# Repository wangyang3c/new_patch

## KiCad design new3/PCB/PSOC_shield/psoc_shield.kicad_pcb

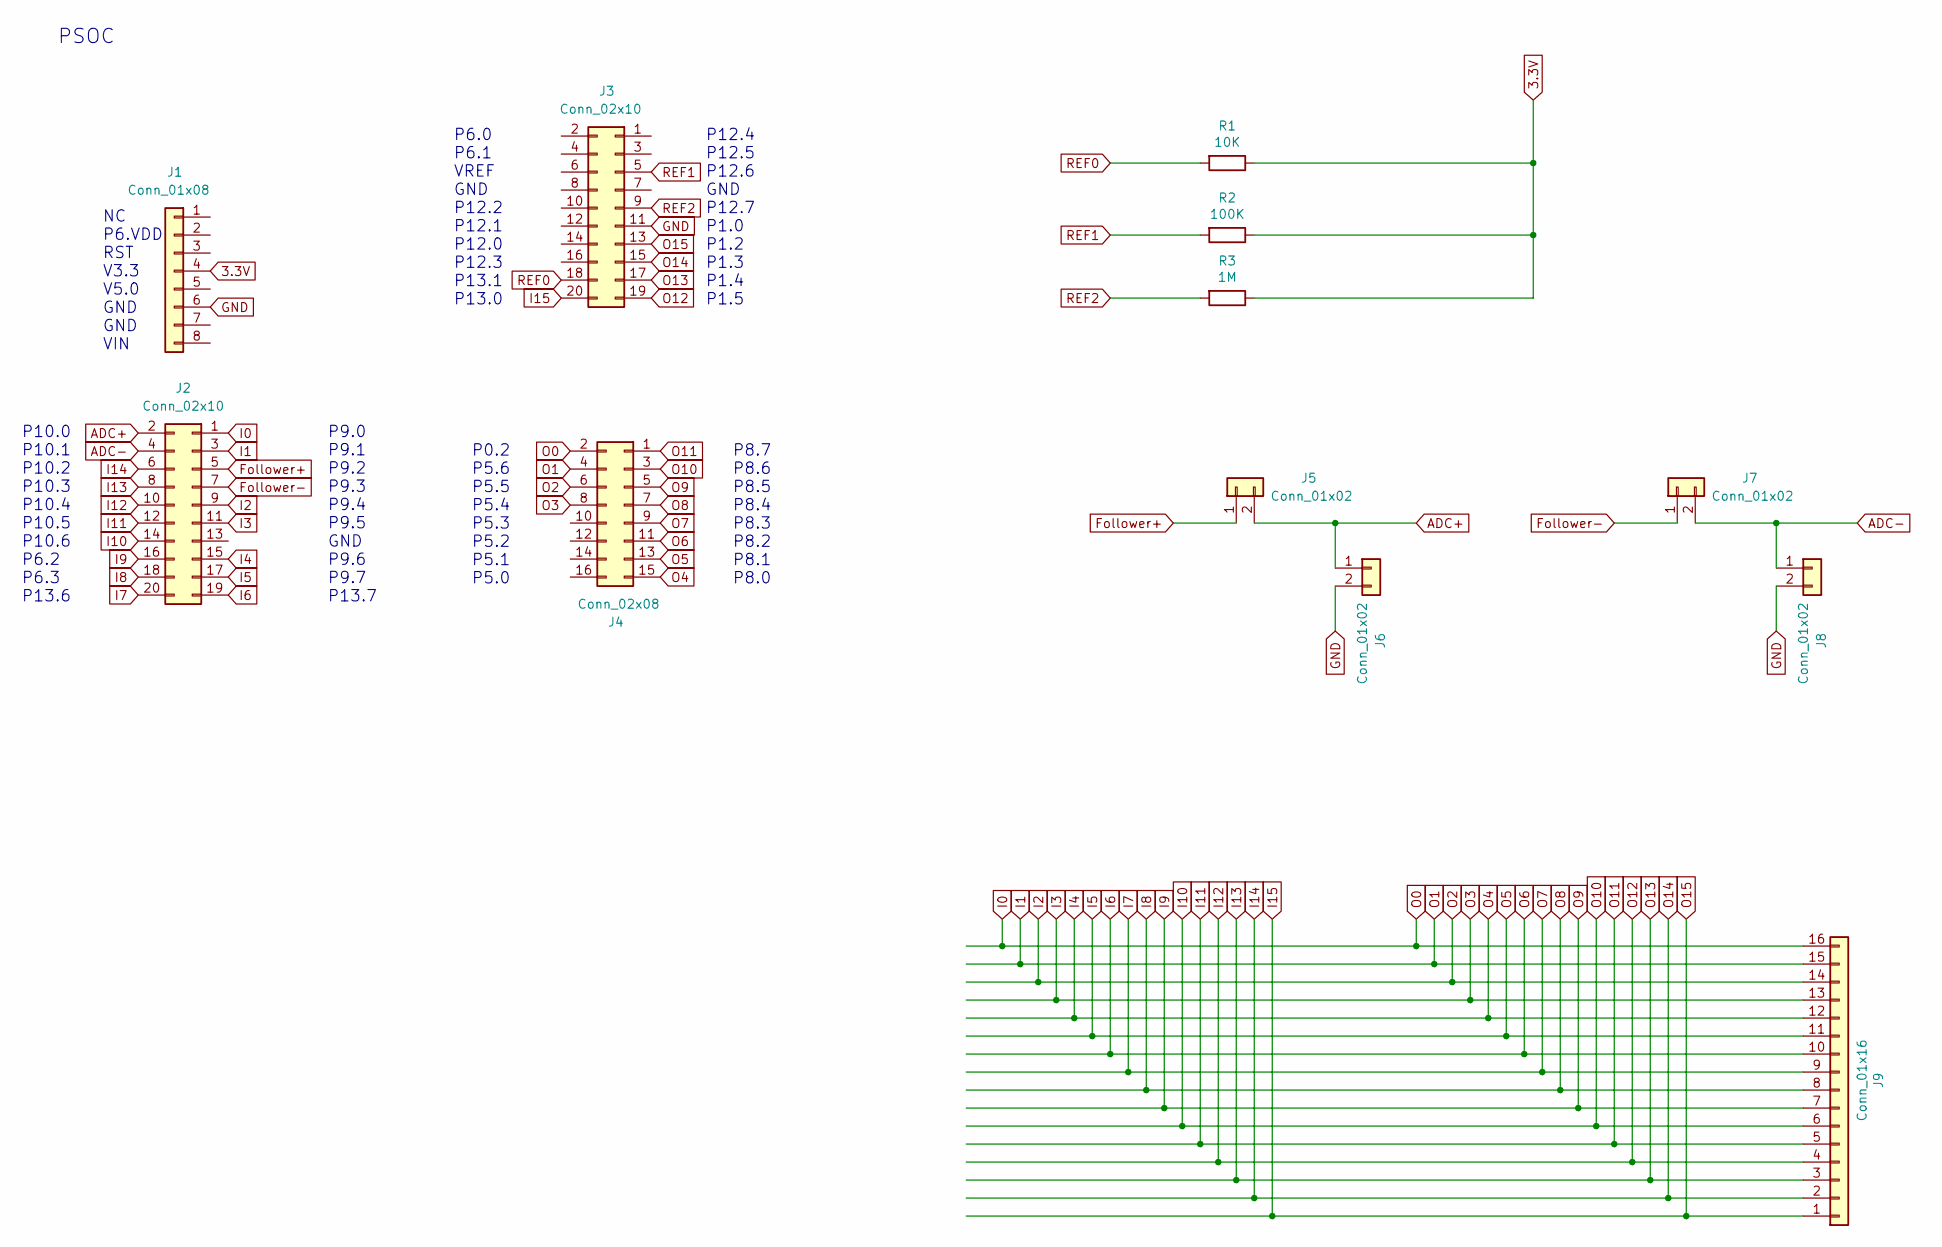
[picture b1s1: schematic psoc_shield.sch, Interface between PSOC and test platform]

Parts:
J1: Conn_01x08; PinSocket_1x08_P2.54mm_Vertical
J2, J3: Conn_02x10; PinSocket_2x10_P2.54mm_Vertical
J4: Conn_02x08; PinSocket_2x08_P2.54mm_Vertical
J5, J6, J7, J8: Conn_01x02; PinSocket_1x02_P2.54mm_Vertical
J9: Conn_01x16; FH19SC16S05SH09
R1: 10K; R_0805_2012Metric
R2: 100K; R_0805_2012Metric
R3: 1M; R_0805_2012Metric

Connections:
3.3V: J1.4, R1.1, R2.1, R3.1
ADC+: J2.2, J5.2, J6.1
ADC-: J2.4, J7.2, J8.1
Follower+: J2.5, J5.1
Follower-: J2.7, J7.1
GND: J1.6, J3.11, J6.2, J8.2
I0: J2.1, J4.2, J9.16
I1: J2.3, J4.4, J9.15
I2: J2.9, J4.6, J9.14
I3: J2.11, J4.8, J9.13
I4: J2.15, J4.15, J9.12
I5: J2.17, J4.13, J9.11
I6: J2.19, J4.11, J9.10
I7: J2.20, J4.9, J9.9
I8: J2.18, J4.7, J9.8
I9: J2.16, J4.5, J9.7
I10: J2.14, J4.3, J9.6
I11: J2.12, J4.1, J9.5
I12: J2.10, J3.19, J9.4
I13: J2.8, J3.17, J9.3
I14: J2.6, J3.15, J9.2
I15: J3.13, J3.20, J9.1
REF0: J3.18, R1.2
REF1: J3.5, R2.2
REF2: J3.9, R3.2

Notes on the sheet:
PSOC
P10.0 P10.1 P10.2 P10.3 P10.4 P10.5 P10.6 P6.2 P6.3 P13.6
P9.0 P9.1 P9.2 P9.3 P9.4 P9.5 GND P9.6 P9.7 P13.7
P8.7 P8.6 P8.5 P8.4 P8.3 P8.2 P8.1 P8.0
P0.2 P5.6 P5.5 P5.4 P5.3 P5.2 P5.1 P5.0
P12.4 P12.5 P12.6 GND P12.7 P1.0 P1.2 P1.3 P1.4 P1.5
P6.0 P6.1 VREF GND P12.2 P12.1 P12.0 P12.3 P13.1 P13.0
NC P6.VDD RST V3.3 V5.0 GND GND VIN

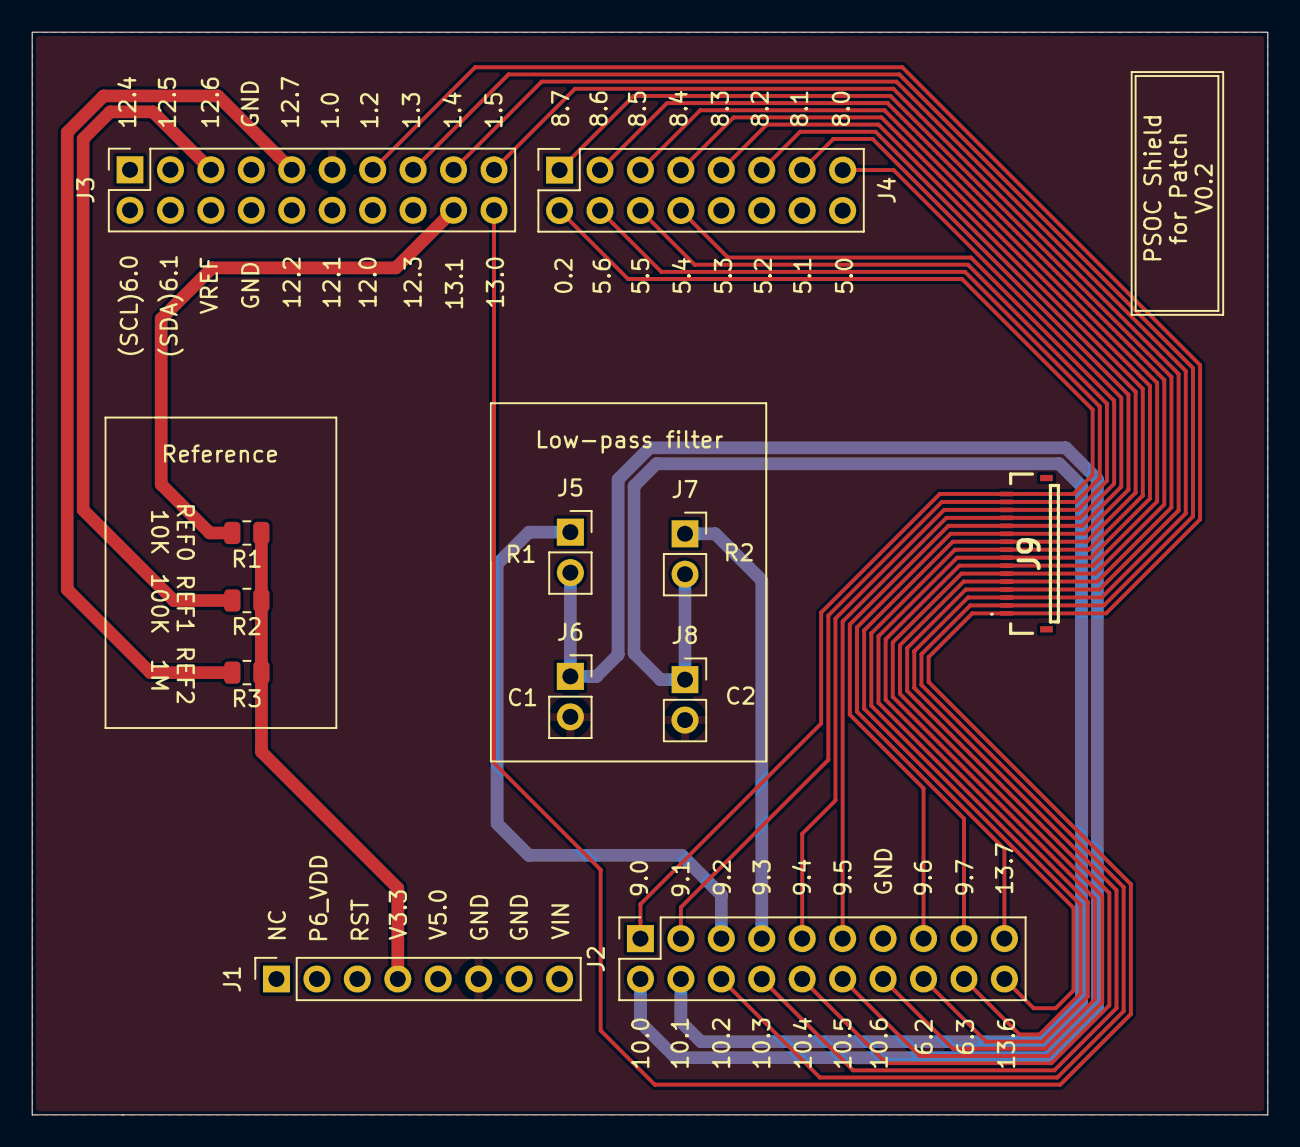
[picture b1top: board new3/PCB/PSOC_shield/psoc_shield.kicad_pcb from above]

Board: 2 copper layers, 77.6 x 68.0 mm, 12 parts (0 on the bottom side), 25 nets.

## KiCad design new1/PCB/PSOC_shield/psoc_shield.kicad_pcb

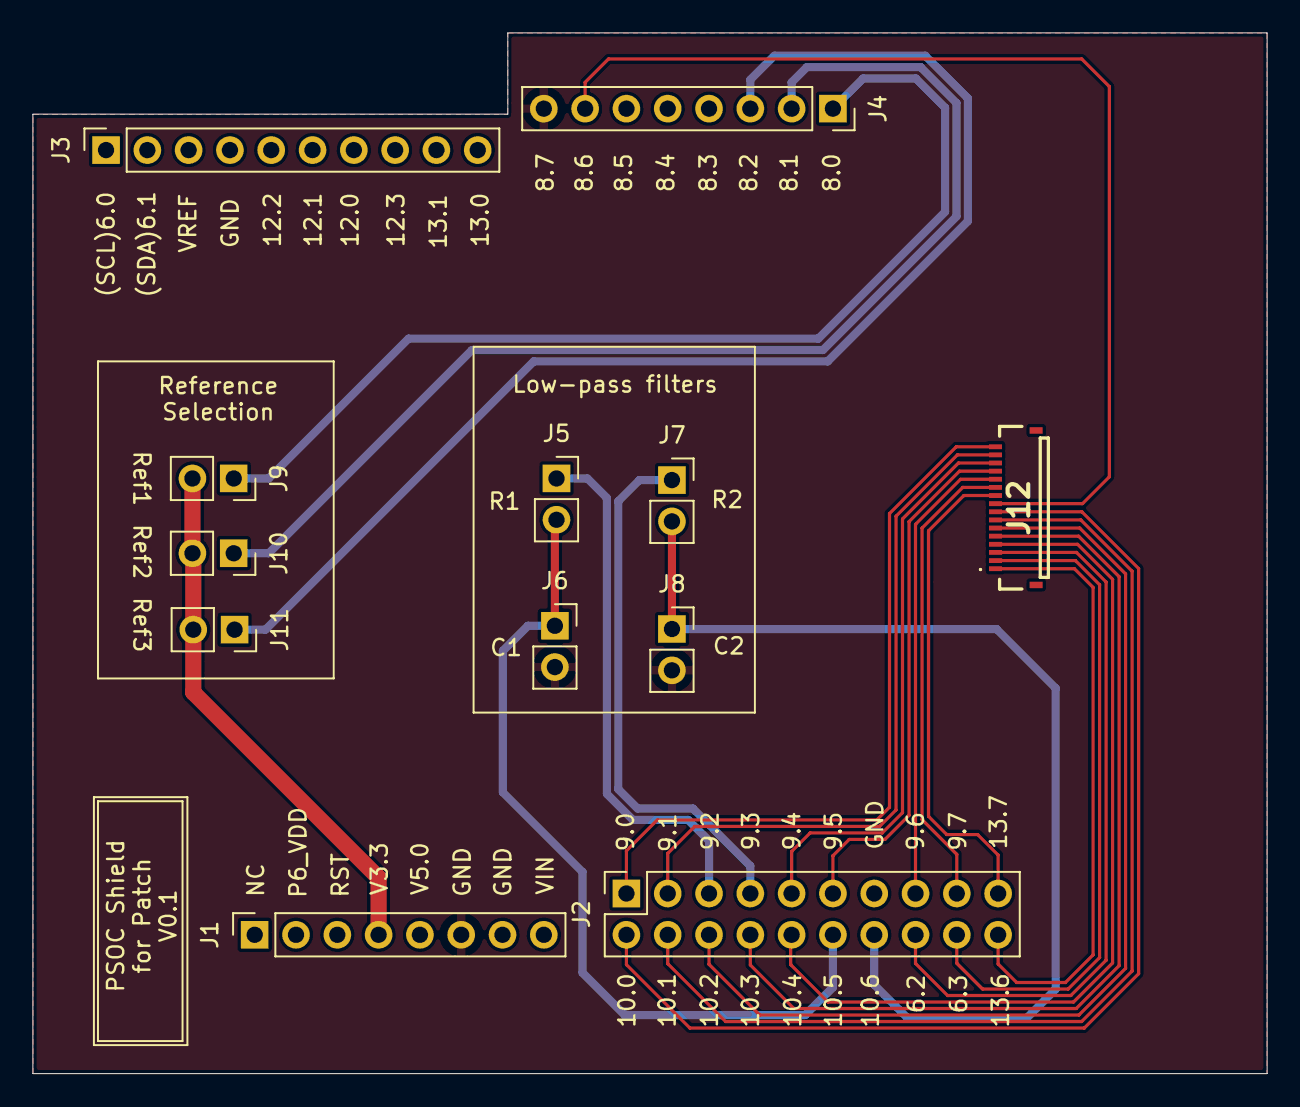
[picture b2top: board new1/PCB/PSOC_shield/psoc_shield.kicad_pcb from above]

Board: 2 copper layers, 75.9 x 64.0 mm, 12 parts (0 on the bottom side), 25 nets.

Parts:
J1, J4: Conn_01x08; PinSocket_1x08_P2.54mm_Vertical
J2: Conn_02x10; PinSocket_2x10_P2.54mm_Vertical
J3: Conn_01x10; PinSocket_1x10_P2.54mm_Vertical
J5, J6, J7, J8, J9, J10, J11: Conn_01x02; PinSocket_1x02_P2.54mm_Vertical
J12: Conn_01x16; FH19SC16S05SH09

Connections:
3.3V: J1.4, J9.2, J10.2, J11.2
ADC+: J2.12, J5.2, J6.1
ADC-: J2.14, J7.2, J8.1
Follower+: J2.5, J5.1
Follower-: J2.7, J7.1
GND: J1.6, J4.8, J6.2, J8.2
I0: J2.1, J12.16
I1: J2.3, J12.15
I2: J2.9, J12.14
I3: J2.11, J12.13
I4: J2.15, J12.12
I5: J2.17, J12.11
I6: J2.19, J12.10
I7: J4.7, J12.9
O0: J2.2, J12.8
O1: J2.4, J12.7
O2: J2.6, J12.6
O3: J2.8, J12.5
O4: J2.10, J12.4
O5: J2.16, J12.3
O6: J2.18, J12.2
O7: J2.20, J12.1
R_ref1: J4.1, J9.1
R_ref2: J4.2, J10.1
R_ref3: J4.3, J11.1

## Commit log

2022-03-01 Create project
2022-03-04 new protocol implementation
2022-03-04 small changes
2022-03-05 update protocol
2022-03-05 implement resistance code
2022-03-06 fix resistance code
2022-04-01 update protocol explanation
2022-05-23 add new3
